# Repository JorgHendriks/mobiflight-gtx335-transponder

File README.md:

# GTX 335 Flight-Simulator Transponder

A DIY desktop flight-simulator transponder inspired by the Garmin GTX 335 and designed for use with [MobiFlight](https://www.mobiflight.com/). The project combines a custom PCB, a 3D-printed and laser-engraved enclosure, and MobiFlight community firmware.

> [!IMPORTANT]
> This is an unofficial hobby project for flight simulation. It is not a real transponder, does not transmit ADS-B or radio signals, is not certified for aviation use, and is not affiliated with or endorsed by Garmin.

## Features

- Raspberry Pi Pico-based board with a 3.12-inch OLED and 20 illuminated buttons
- Most functions of the real GTX 335 are implemented, including transponder, altitude, and timer functions
- Preconfigured MobiFlight firmware and an example Microsoft Flight Simulator 2024 project

## Repository contents

| Folder | Contents |
|---|---|
| [`pcb`](pcb/README.md) | KiCad source, schematic, bill of materials, component notes, and ready-to-order fabrication archive |
| [`mechanical`](mechanical/README.md) | FreeCAD source, printable parts, laser artwork, print settings, and enclosure assembly notes |
| [`firmware`](firmware/README.md) | MobiFlight community firmware source and build instructions |
| [`firmware/MF_Configs`](firmware/MF_Configs) | Board configuration backup and an example MSFS 2024 MobiFlight project |

## What you need

- The components listed in the [PCB bill of materials](pcb/README.md#bill-of-materials)
- A manufactured and assembled PCB
- The hardware, printed enclosure parts and engraved controls described in the [enclosure guide](mechanical/README.md)
- A Windows PC running [MobiFlight](https://www.mobiflight.com/)
- Microsoft Flight Simulator 2024 if you want to use the included example project

## Quick start

### 1. Build the hardware

Order and assemble the board by following the [PCB guide](pcb/README.md), then print, engrave, and assemble the controls and enclosure by following the [mechanical guide](mechanical/README.md).

Pay particular attention to the OLED configuration and LED polarity of the switches.

### 2. Install the community firmware package

1. Download `GTX335_<version>.zip` from the [latest GitHub release](../../releases/latest).
2. Extract the archive into:

   ```text
   %LocalAppData%\MobiFlight\MobiFlight Connector\Community
   ```

   The resulting directory should be `Community\GTX335`.
3. Restart MobiFlight.
4. Connect the panel over USB and open **Extras > Settings > MobiFlight Modules**.
5. If necessary, reset the Pico from its board context menu. Then choose **Update firmware > Community > JH GTX335**.

The custom device and its twenty named buttons are stored in the firmware configuration, so a manual pin-by-pin setup is not normally required. For screenshots and more detail, see MobiFlight's [Community Board and Custom Devices user guide](https://github.com/MobiFlight/MobiFlight-Connector/wiki/User-guide-%E2%80%90-Community-Board-and-Custom-Devices).

If preferred, build a package from source by following the [firmware build instructions](firmware/README.md).

### 3. Load the MSFS 2024 example project

1. In MobiFlight 11 or newer, open [`firmware/MF_Configs/GTX335_MSFS2024.mfproj`](firmware/MF_Configs/GTX335_MSFS2024.mfproj), or merge its profile into an existing project.
2. If MobiFlight reports a missing controller, use **Extras > Controller Bindings** to bind the profile to the connected `JH GTX335`.
3. Start Microsoft Flight Simulator 2024, load an aircraft, and click **Run** in MobiFlight.

See the MobiFlight documentation for [opening and merging projects](https://docs.mobiflight.com/features/projects/) and [updating controller bindings](https://docs.mobiflight.com/features/controller-bindings/).

The included profile targets the generic MSFS 2024 transponder variables and events. Aircraft with custom avionics may need their own MobiFlight presets or calculator-code mappings.

## Current limitations

- Flight ID is display-only and cannot be entered from the panel.
- The SYS menu is only partially implemented.

## Building the firmware

Developer prerequisites, the PlatformIO command, generated files, and release-version handling are documented in [`firmware/README.md`](firmware/README.md).

## Licence

The firmware is available under the [MIT License](firmware/LICENSE). The PCB, 3D models, fabrication files, artwork, and project documentation are available for non-commercial use under [CC BY-NC-SA 4.0](LICENSE.md).

Third-party names and trademarks are not included in these licences. See the [complete licensing details](LICENSE.md).

## Contributing

Bug reports, tested aircraft mappings, firmware improvements, and fabrication feedback are welcome. When reporting a hardware problem, include the PCB revision, Pico and OLED variants, MobiFlight version, simulator and aircraft, and clear photos where relevant.

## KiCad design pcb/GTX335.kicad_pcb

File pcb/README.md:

# PCB

## PCB manufacturing

The fabrication files for the latest PCB are included in:

[Download the GTX335 v1.1 PCB fabrication files](./GTX335_v1_1_pcb_fab.zip)

Upload the ZIP archive directly to your PCB manufacturer and select a standard board thickness of **1.6 mm**.

## Schematic

[View the full-resolution schematic](GTX335_Schematic.pdf)

## Bill of materials

| Designators | Quantity | Component | Specification |
|---|---:|---|---|
| SW1-SW20 | 20 | Illuminated tactile switch | 6 x 6 x 7.2 mm, six pins, white LED |
| R1-R20 | 20 | Resistor | 220 ohm, 1206 package |
| R21, R22 | 2 | Resistor | 10 kohm, 1206 package |
| Q1 | 1 | NPN transistor | BC847, SOT-23 package |
| Q2 | 1 | P-channel MOSFET | AO3401A, SOT-23 package |
| J1 | 1 | Socket header | 2 x 8 pins, 2.54 mm pitch, vertical |
| A1 | 2 | Female socket header | 20 pins, 2.54 mm pitch |
| - | 1 | Microcontroller board | Raspberry Pi Pico v1 |
| - | 1 | OLED display | 3.12-inch, 256 x 64 pixels, SSD1322 controller |

## Parts

### Illuminated tactile switches

Use twenty illuminated tactile switches with the following specifications:

- Body size: 6 x 6 mm
- Total height: 7.2 mm
- Number of pins: 6
- Integrated LED colour: white
- Switch contact: normally open

[6 x 6 x 7.2 mm illuminated tactile switch with white LED](https://nl.aliexpress.com/item/1005008121502218.html)

Four pins form the two duplicated switch contacts. The remaining two pins connect the integrated LED.

Verify the dimensions, height, and six-pin layout before ordering. Similar-looking 6 x 6 mm switches may use a different height, LED polarity, pin arrangement, or PCB footprint.

### OLED display

Use a 3.12-inch graphic OLED module with the following specifications:

- Resolution: 256 x 64 pixels
- Controller: SSD1322
- Interface: 4-wire SPI
- Connector: 16 pins
- Module width: approximately 100.5 mm
- Module height: approximately 33.5 mm

[SSD1322 3.12-inch 256 x 64 OLED display](https://nl.aliexpress.com/item/1005003091450549.html)

Check the specs carefully as some OLED screens are sold without the interface board or with different chipsets.

#### OLED pinout

| Pin | Symbol | Function | Use in 4-wire SPI mode |
|---:|---|---|---|
| 1 | VSS | Power-supply ground | Ground |
| 2 | VCC_IN | Positive power supply | Power |
| 3 | NC | Not connected | Not used |
| 4 | D0/CLK | Parallel data D0 / serial clock | SPI clock |
| 5 | D1/DIN | Parallel data D1 / serial data | SPI data |
| 6 | D2 | Parallel data D2 | Not used |
| 7 | D3 | Parallel data D3 | Not used |
| 8 | D4 | Parallel data D4 | Not used |
| 9 | D5 | Parallel data D5 | Not used |
| 10 | D6 | Parallel data D6 | Not used |
| 11 | D7 | Parallel data D7 | Not used |
| 12 | E/RD# | Enable / read | Not used after interface configuration |
| 13 | R/W# | Read / write | Not used after interface configuration |
| 14 | D/C# | Data / command selection | Data/command |
| 15 | RES# | Reset | Reset |
| 16 | CS# | Chip selection | Chip select |

### Raspberry Pi Pico

Use a **Raspberry Pi Pico v1** fitted with two 20-pin, 2.54 mm pitch headers.

The PCB is designed for the original RP2040-based Raspberry Pi Pico. Other Pico variants are not currently supported.

Install the Pico in the two corresponding 20-pin header rows on the PCB.

## Assembly notes

### Configure the OLED for 4-wire SPI

Before installing the OLED module, configure it for the **4-wire SPI interface**. This mode may be marked as **4SPI** on the display PCB.

Configure the interface-selection jumpers by soldering the required **0 ohm jumper resistors** according to the 4SPI configuration shown for the module.

### Install the illuminated tactile switches

Each tactile switch contains a polarity-sensitive LED.

The **small square PCB pad is ground** and must connect to the negative LED terminal (short).

To test the switch LEDs during assembly, apply 3–5 V DC to pin 2 of the EXT LED connector and connect the supply ground to any PCB ground point.

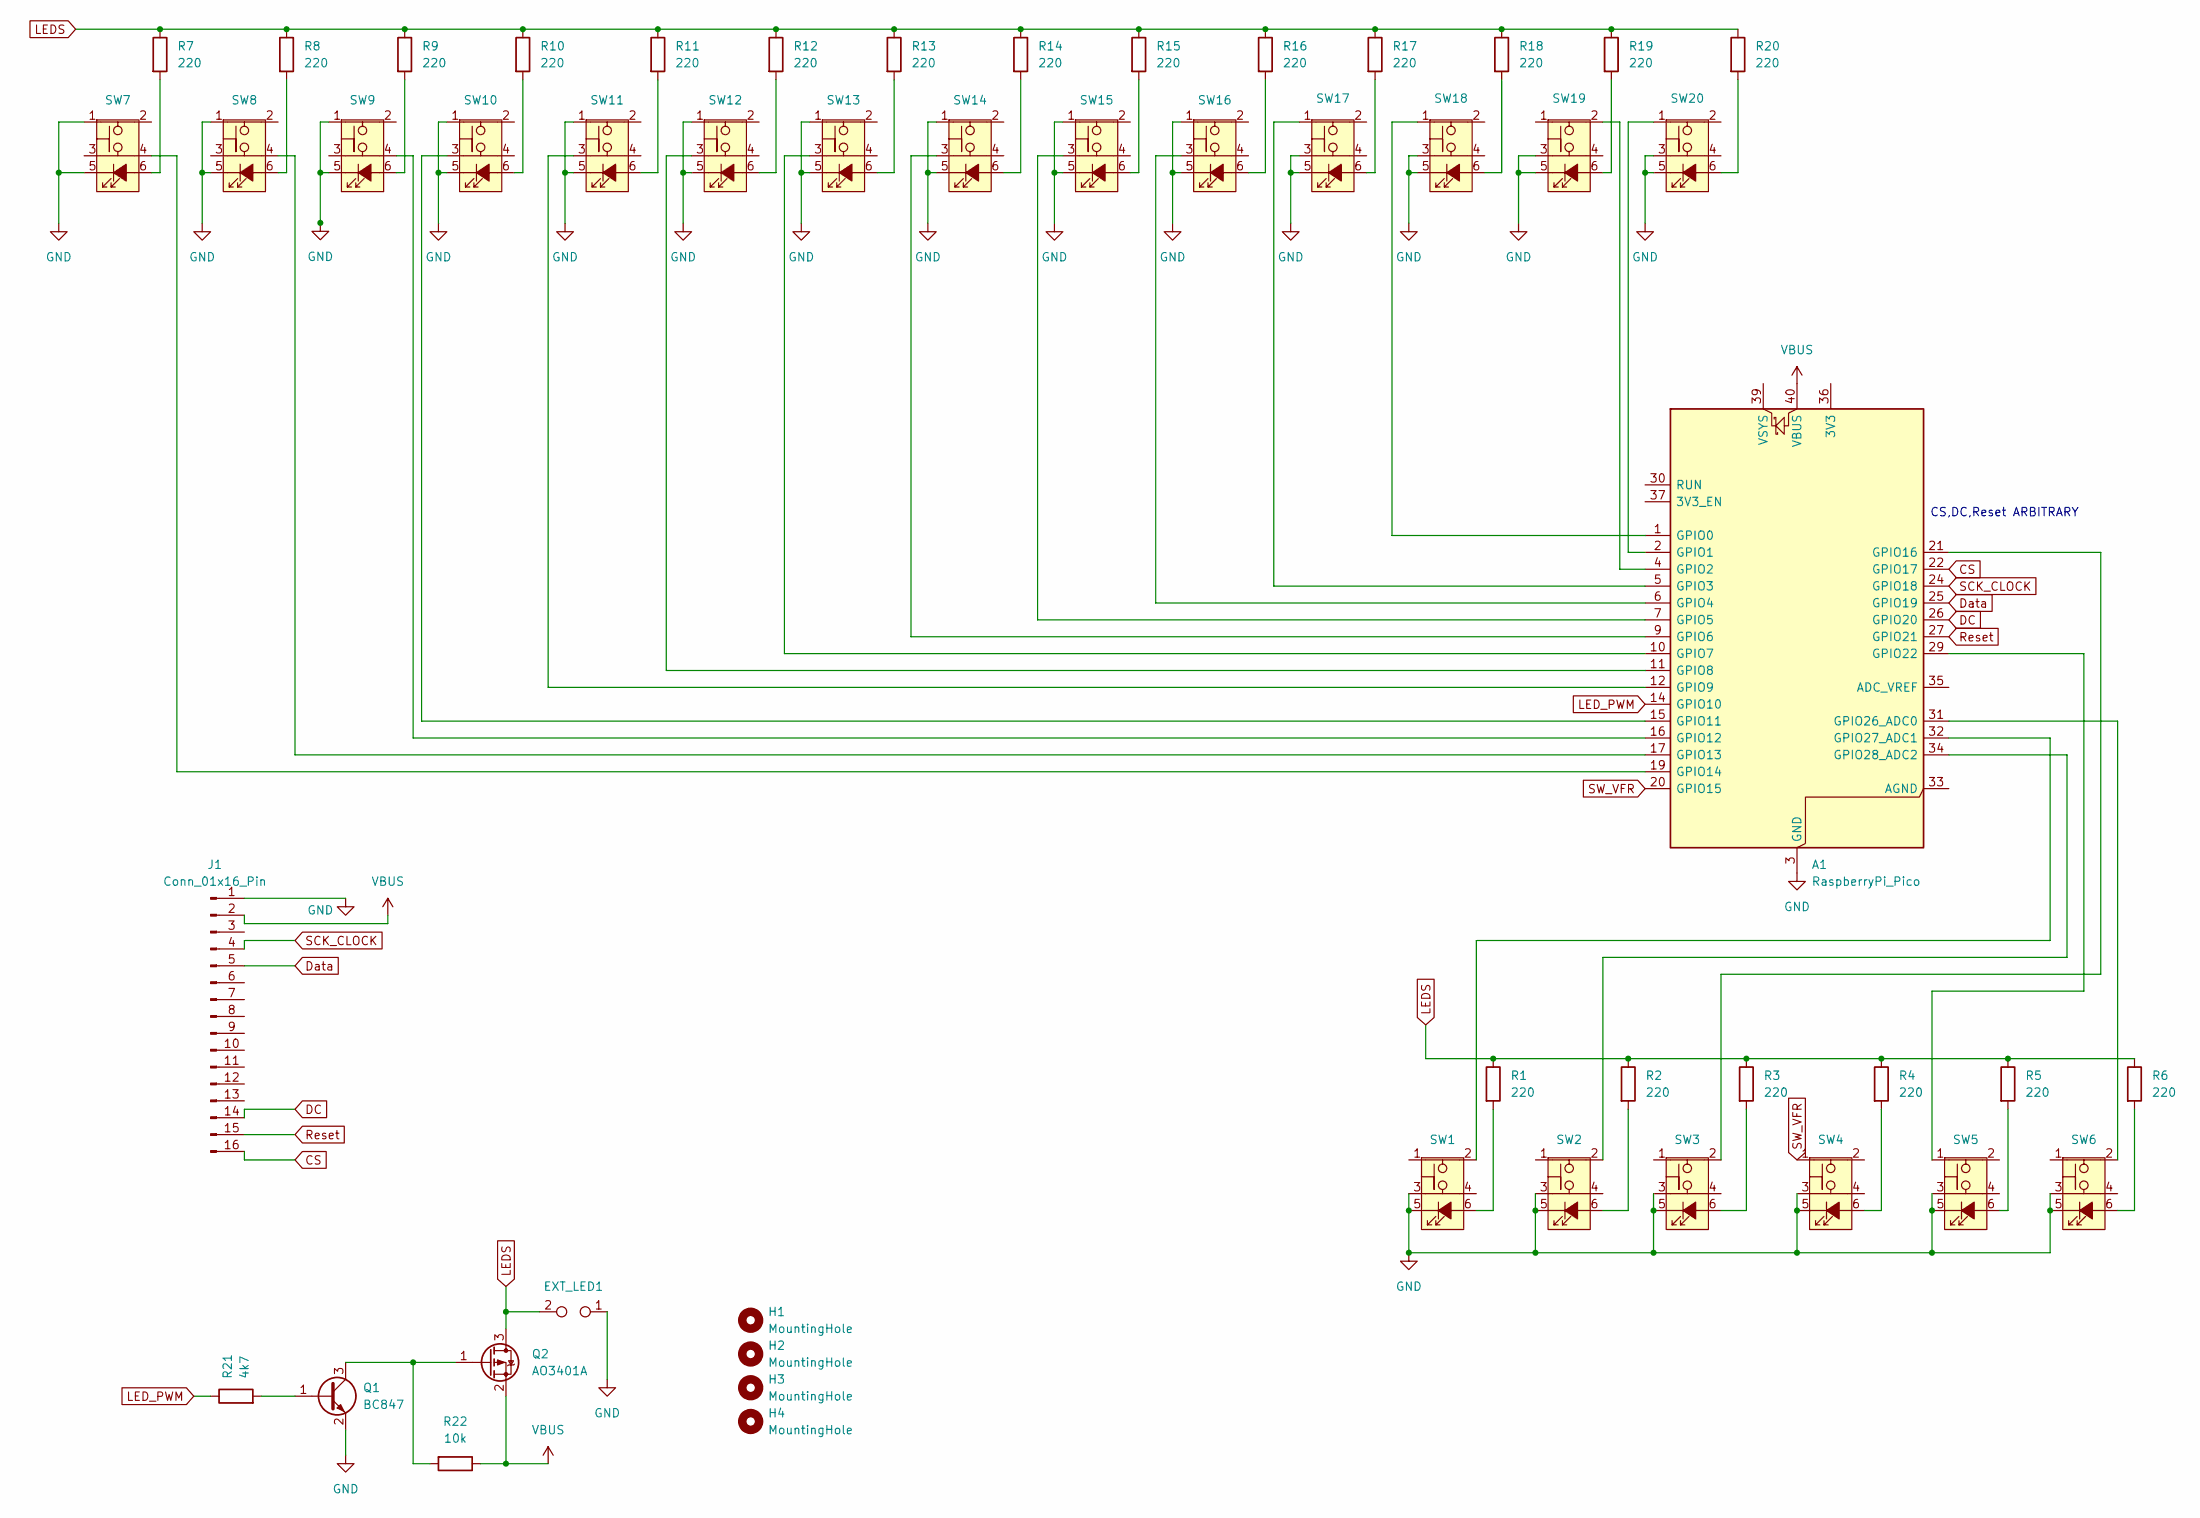
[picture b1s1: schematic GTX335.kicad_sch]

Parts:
A1: RaspberryPi_Pico; RaspberryPi_Pico_Common_Unspecified
EXT_LED1: TestPoint_2Pole; PinHeader_2x01_P2.54mm_Vertical
H1, H2, H3, H4: MountingHole; MountingHole_2.2mm_M2
J1: Conn_01x16_Pin; PinSocket_2x08_P2.54mm_Vertical
Q1: BC847; SOT-23
Q2: AO3401A; SOT-23
R1, R2, R3, R4, R5, R6, R7, R8, R9, R10, R11, R12, R13, R14, R15, R16, R17, R18, R19, R20: 220; R_1206_3216Metric
R21: 4k7; R_1206_3216Metric
R22: 10k; R_1206_3216Metric
SW1, SW2, SW3, SW4, SW5, SW6, SW7, SW8, SW9, SW10, SW11, SW12, SW13, SW14, SW15, SW16, SW17, SW18, SW19, SW20: SW_Push_LED_6p; SW_PUSH_LED_6mm_H7.2mm

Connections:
CS: A1.22 (GPIO17), J1.16
DC: A1.26 (GPIO20), J1.14
Data: A1.25 (GPIO19), J1.5
GND: A1.3 (GND), A1.8 (GND), A1.13 (GND), A1.18 (GND), A1.23 (GND), A1.28 (GND), A1.38 (GND), EXT_LED1.1, J1.1, Q1.2 (E), SW1.3, SW1.5 (K), SW2.3, SW2.5 (K), SW3.3, SW3.5 (K), SW4.3, SW4.5 (K), SW5.3, SW5.5 (K), SW6.3, SW6.5 (K), SW7.1, SW7.5 (K), SW8.1, SW8.5 (K), SW9.1, SW9.5 (K), SW10.1, SW10.5 (K), SW11.1, SW11.5 (K), SW12.1, SW12.5 (K), SW13.1, SW13.5 (K), SW14.1, SW14.5 (K), SW15.1, SW15.5 (K), SW16.1, SW16.5 (K), SW17.3, SW17.5 (K), SW18.3, SW18.5 (K), SW19.3, SW19.5 (K), SW20.3, SW20.5 (K)
LEDS: EXT_LED1.2, Q2.3 (D), R1.1, R2.1, R3.1, R4.1, R5.1, R6.1, R7.1, R8.1, R9.1, R10.1, R11.1, R12.1, R13.1, R14.1, R15.1, R16.1, R17.1, R18.1, R19.1, R20.1
LED_PWM: A1.14 (GPIO10), R21.1
unnamed: A1.1 (GPIO0), SW18.1
unnamed: A1.2 (GPIO1), SW20.1
unnamed: A1.4 (GPIO2), SW19.2
unnamed: A1.5 (GPIO3), SW17.1
unnamed: A1.6 (GPIO4), SW16.3
unnamed: A1.7 (GPIO5), SW15.3
unnamed: A1.9 (GPIO6), SW14.3
unnamed: A1.10 (GPIO7), SW13.3
unnamed: A1.11 (GPIO8), SW12.3
unnamed: A1.12 (GPIO9), SW11.3
unnamed: A1.15 (GPIO11), SW10.3
unnamed: A1.16 (GPIO12), SW9.4
unnamed: A1.17 (GPIO13), SW8.4
unnamed: A1.19 (GPIO14), SW7.4
unnamed: A1.21 (GPIO16), SW3.2
unnamed: A1.29 (GPIO22), SW5.1
unnamed: A1.31 (GPIO26_ADC0), SW6.2
unnamed: A1.32 (GPIO27_ADC1), SW1.2
unnamed: A1.34 (GPIO28_ADC2), SW2.2
unnamed: Q1.1 (B), R21.2
unnamed: Q1.3 (C), Q2.1 (G), R22.2
unnamed: R1.2, SW1.6
unnamed: R2.2, SW2.6
unnamed: R3.2, SW3.6
unnamed: R4.2, SW4.6
unnamed: R5.2, SW5.6
unnamed: R6.2, SW6.6
unnamed: R7.2, SW7.6
unnamed: R8.2, SW8.6
unnamed: R9.2, SW9.6
unnamed: R10.2, SW10.6
unnamed: R11.2, SW11.6
unnamed: R12.2, SW12.6
unnamed: R13.2, SW13.6
unnamed: R14.2, SW14.6
unnamed: R15.2, SW15.6
unnamed: R16.2, SW16.6
unnamed: R17.2, SW17.6
unnamed: R18.2, SW18.6
unnamed: R19.2, SW19.6
unnamed: R20.2, SW20.6
Reset: A1.27 (GPIO21), J1.15
SCK_CLOCK: A1.24 (GPIO18), J1.4
SW_VFR: A1.20 (GPIO15), SW4.1
VBUS: A1.40 (VBUS), J1.2, Q2.2 (S), R22.1

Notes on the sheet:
CS,DC,Reset ARBITRARY

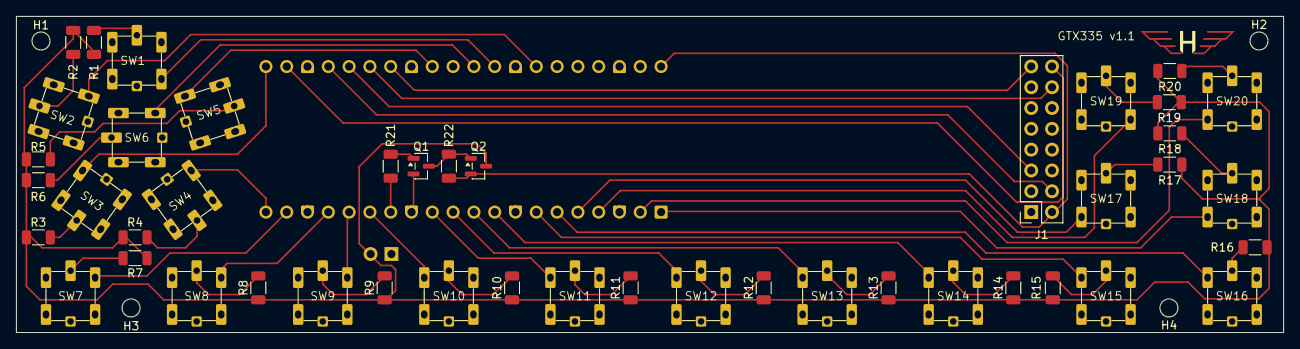
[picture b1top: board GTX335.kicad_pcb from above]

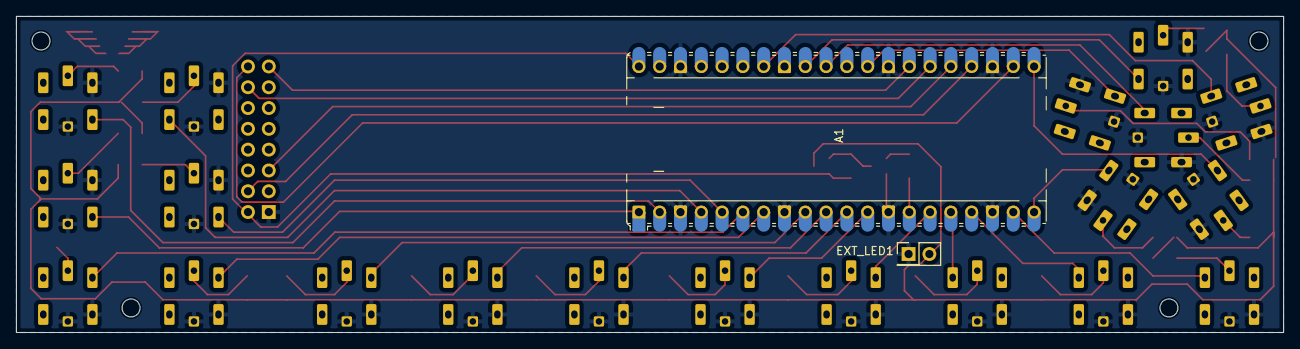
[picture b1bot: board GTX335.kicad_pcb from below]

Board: 2 copper layers, 154.8 x 38.6 mm, 51 parts (2 on the bottom side), 51 nets.
